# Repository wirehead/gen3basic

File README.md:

# gen3basic Wiring/Arduino compatible LED light board

This is a programmable light-painting instrument that looks enough like an Arduino board to use the Arduino studio and the Wiring library.  It has 3 through-hole 5mm LEDs, 3 5050 APA102 LEDs, 3 buttons, a set of screw terminals deliberately designed to be exactly like the terminals on a [PixelBlaze](https://www.bhencke.com/pixelblaze) for controlling external LED strings, and a non-shield-compatible set of breakout pins that are all on a 0.1" / 2.54mm grid.

## Prior art

I've got a pair of really old boards.  They both have 40 pin ATMega16's and some LEDs.  One has 8 LEDs so it works as a POV.  The other has 3 RGB LEDs.  I didn't really use them very much.

The things I did really wrong with them are:

 * No buttons!  This is actually really annoying because most of the standard modern buttons don't quite fit in a perfboard and so just finding buttons was annoying.  Therefore, I'd guess at what color I wanted as a pattern and then it wouldn't be right when I pulled it out during a shoot.
 * One of them was programmed in AVR assembler, the other one was programmed in AVR GCC.  No libraries.  The whole toolchain was a bit annoying and the problem is that I can do everything from scratch in assembly language and it's fun to play around with assembly language, but if you want to get something done, use the highest level tool that fits your needs.

## But first, why Prolific is a bunch of jerks

Anyway, the two boards moldered in my collection for a long time, then I decided that it was time to do some electronics stuff and pulled the cart that's always had my electronics on it out of the closet and set it up next to my computer, and started working on it again.

Really the only hitch is that apparently my Monoprice USB to Serial converter contains what may be a fake Prolific chip and Prolific's drivers were changed so as to intentionally not work with any of the fake chips by giving you an unhelpful error message.  So I had to get a new USB to serial cable.

Like, cool, I get that Prolific spent a lot of time and energy making a USB chip and they don't see any of the money from when some random factory decides to clone their chip.  But what this means for me is that Prolific took their annoyance upon parties who are not me out on me.

Also, FTDI has done the same thing.

So I was all set to do some AVR programming work, having rolled out my workbench cart with the STK-500 and my serial adapter... and then I had to hurry up and pick up another USB-to-RS232 cable.

## The design

Design goals:

 * Be useful for light painting
 * Have some single-spectrum LEDs in a commonly available size available.
 * Have some RGB LEDs also available.
 * Be able to control an external string of RGB LEDs.
 * Have some buttons for control, so I could switch programs.
 * Use some surface mount parts, but not do everything surface mount, so I wouldn't realize partway through fabbing the board that I'd made a poor life choice.
 * Be a 2 layer 5cm x 5cm board so I can fab it at places like DirtyPCB's.
 * Not be overly ambitious or complicated in any particular direction.
 * Be able to be programmed using a friendly Arduino environment.
 * Be able to be re-purposed as a general-purpose Arduino-esque design.
 * Not require me to have the full electronics workbench out to mess with it.

Various design thoughts:

 * Buttons!  Okay, so I've got the [PixelBlaze](https://www.bhencke.com/pixelblaze).  I've got a fully soldered and functional [MiniPOV 4 Kit](https://www.adafruit.com/product/1776) from Adafruit.  The MiniPOV is running up against a limit of how much EEPROM the AVR has so it really only can do one pattern.  The PixelBlaze is better because it's running equations and it's got WiFi anyway so I can just use a computer to tweak at the settings.  I decided to squeeze in 3 buttons because I know I need to change programs and I need to 'mute' the light so my lines can have a defined beginning and end and I'll probably really want to add at least one more later on.
 * Tactile cues are very important in the dark, which is why the corners all are different shapes and there's a pair of indents on the sides.  
 * I HATE LED MANUFACTURERS AND THEIR RANDOM SELECTION OF FOOTPRINTS.  Like, what I want is to pick a shape that lets me get at some LEDs that are available in a wide variety of colors other than the standard RGB wavelengths.  So I ended up just putting in the holes for 5mm because that still has a reasonably wide selection and no LED manufacturers screwing with the footprints.
 * There's a bunch of surface mount parts here.  I decided that, if you have a professionally manufactured PCB with solder masks and stuff, it's kinda silly to not use some 1206 or 0805 surface mount bits.
 * The reset circuitry fairly closely follows the Arduino model as well as the recommendations from AN2519, which suggests that you not only have a pull-up resistor but also a diode.
 * There are resistors in the MOSI and SCK nets, also a recommendation from AN2519, because otherwise it totally failed to work when I had it wired up on a breadboard with the AVR, the STK-500, and the APA102s.
 * Instead of a resonator like the Arduino, I use a crystal.  Mostly because it's kinda obvious that maybe I'd want to use it for a clock-like thing and a crystal is better for that.
 * I'm not putting an LED on the SCK line, which is one deviation from the standard Arduino form factor.  The last thing I want is a little glowing light while the APA's are being controlled and there's reasons why that's OK on a real Arduino and not mine.
 * I really want to make my board able to have a piece of perfboard with headers plugged in above it, which is one of several reasons why this is not using Arduino shields.  At the same time, the more pins I broke out, the harder the routing got, so I didn't break all of them out.
 * I meant to put a SOD-123 but I accidentally put a tiny SOD-323 instead.
 * Overall, I learned a lot from [Bald Engineer's DIY Arduino article](https://www.baldengineer.com/diy-arduino-schematic-checklist.html) and [Rheingold Heavy's Arduino From Scratch series](https://rheingoldheavy.com/category/education/fundamentals/arduino-from-scratch-series/).

I used [KiCad](http://kicad-pcb.org/) for schematic capture and PCB layout.

## BOM

| Reference    |  Quantity |  Value                                  |  Footprint                                                   |  Digi-Key_PN        |  Manufacturer_PN     |  Notes                                                                        |  Spec   | 
|--------------|-----------|-----------------------------------------|--------------------------------------------------------------|---------------------|----------------------|-------------------------------------------------------------------------------|---------| 
| C1 C2        | 2         | 22pF                                    | `Capacitor_SMD:C_0805_2012Metric_Pad1.15x1.40mm_HandSolder`    | 399-8036-1-ND       | C0805C220K5GACTU     |                                                                               | C0G     | 
| C3 C5 C7 C6  | 4         | 100nF                                   | `Capacitor_SMD:C_0805_2012Metric_Pad1.15x1.40mm_HandSolder`    | 1276-6840-1-ND      | CL21B104KCFNNNE      |                                                                               | X7R     | 
| C4 C8        | 2         | 47uF                                    | `Capacitor_THT:CP_Radial_D4.0mm_P1.50mm`                       | 493-12770-1-ND      | UVR1C470MDD6TP       |                                                                               | 20% 16V | 
| D1 D5 D4     | 3         | LED                                     | `LED_THT:LED_D5.0mm_Clear`                                     |                     |                      | Any random 5mm LED works, adjust matching resistor based on dropout voltage |         | 
| D2           | 1         | LED                                     | `LED_SMD:LED_0805_2012Metric_Pad1.15x1.40mm_HandSolder`        |                     |                      Any 0805 LED works, don't need to populate it                            |         | 
| D3           | 1         | 1N4148WS                                | `Diode_SMD:D_SOD-323`                                          |  1N4148WTPMSCT-ND   | 1N4148W-TP           |                                                                               |         | 
| D6 D7 D8     | 3         | APA102C                                 | `SparkFun-LED:APA102C                                        ` | 1568-1902-ND        | COM-14863            |                                                                               | 5050    | 
| H1 H2 H3     | 3         | MountingHole                            | `MountingHole:MountingHole_2.2mm_M2_ISO7380`                   |                     |                      |                                                                               |         | 
| J1           | 1         | Screw Terminal 01x02                    | `TerminalBlock:TerminalBlock_bornier-2_P5.08mm`                | ED2580-ND           | OSTTA024163          | Power                                                                         |         | 
| J2           | 1         | AVR-ISP-6                               | `Connector_PinHeader_2.54mm:PinHeader_2x03_P2.54mm_Vertical`   | 2057-PH2-06-UA-ND   | PH2-06-UA            | AVR-ISP                                                                       |         | 
| J3           | 1         | Conn 01x06                              | `Connector_PinHeader_2.54mm:PinHeader_1x06_P2.54mm_Vertical`   | 2057-PH1RA-06-UA-ND | PH1RA-06-UA          | Pins breakout                                                                 |         | 
| J4           | 1         | Conn 01x07                              | `Connector_PinHeader_2.54mm:PinHeader_1x07_P2.54mm_Vertical`   | S1012EC-07-ND       | PREC007SAAN-RC       | Pins breakout                                                                 |         | 
| J5           | 1         | Conn 01x08                              | `Connector_PinHeader_2.54mm:PinHeader_1x08_P2.54mm_Vertical`   | 2057-PH1RA-08-UA-ND | PH1RA-08-UA          | Pins breakout                                                                 |         | 
| J6           | 1         | Conn 01x06                              | `Connector_PinHeader_2.54mm:PinHeader_1x06_P2.54mm_Horizontal` | 2057-PH1RA-06-UA-ND |  PH1RA-06-UA         | FTDI-type serial connection                                                   |         | 
| J7           | 1         | Screw Terminal 01x04                    | `TerminalBlock:TerminalBlock_bornier-4_P5.08mm`                | ED2580-ND           | OSTTA024163          | Connecting to APA102 light strips.  Actually two pieces interlocked           |         | 
| R1           | 1         | 1M                                      | `Resistor_SMD:R_0805_2012Metric_Pad1.15x1.40mm_HandSolder`     | 541-1.0MAZCT-ND     | CRCW08051M00DHEAP    |                                                                               | 5%      | 
| R3 R2        | 2         | 330                                     | `Resistor_SMD:R_0805_2012Metric_Pad1.15x1.40mm_HandSolder`     | A106061CT-ND        | CRG0805F330R         |                                                                               | 5%      | 
| R4           | 1         | 1k                                      | `Resistor_SMD:R_0805_2012Metric_Pad1.15x1.40mm_HandSolder`     | RR12P1.0KDCT-ND     |  RR1220P-102-D       |                                                                               | 5%      | 
| R6           | 1         | 10k                                     | `Resistor_SMD:R_0805_2012Metric_Pad1.15x1.40mm_HandSolder`     | RR12P10.0KDCT-ND    | RR1220P-103-D        |                                                                               | 5%      | 
| R8 R5 R7     | 3         | 1k                                      | `Resistor_SMD:R_1206_3216Metric_Pad1.42x1.75mm_HandSolder`     | P1.0KECT-ND         | ERJ-8GEYJ102V        | Adjust to match LED                                                           | 5% 1/4W | 
| S1           | 1         | EG1224                                  | `Button_Switch_THT:SW_E-Switch_EG1224_SPDT_Angled`             | EG2585-ND           | EG1224               |                                                                               |         | 
| S3 S4 S2     | 3         | MOMENTARY-SWITCH-SPST-SMD-5.2-REDUNDANT | `SparkFun-Switches:TACTILE_SWITCH_SMD_5.2MM`                   | CKN10361CT-ND       | RS-187R05A2-DS MT RT |                                                                               |         | 
| U1           | 1         | ATMEGA328-PU                            | `Package_DIP:DIP-28_W7.62mm_Socket`                            | ATMEGA328-PU-ND     | ATMEGA328P-PU        | Can substitute ATMega8, 88, or 168.                                         |         | 
| Y1           | 1         | 16.0000MHZ 20PF                         | `Crystal:Crystal_HC49-U_Vertical`                              | 887-2015-ND         | 9B-16.000MBBK-B      | Can substitute other 20 pF crystal to change clock speed                      | 20 pF   | 

## Construction

I'm not going to write a tutorial, but here's some pointers:

 * This device is designed for the [MiniCore](https://github.com/MCUdude/MiniCore) so either before you insert the ATMega328 or using J2, you probably want to get that loaded.
 * I designed this to hand-solder the SMT parts.
 * You probably want a 28 pin socket to mount U1.
 * You may not want to populate all of the footprints, see usage below.  You almost certainly want to populate J1, J2, U1, Y1, C1, C2, C3, C4, C5, S1, R6, and D3 to get to a point where you can bootloader the CPU.  

## Usage

### Jacks

This device is designed for around 5v to J1.  There are no regulators or diodes so be careful.  My strategy at present is to connect with a USB cable to a USB power bank for power.

J2 is a 6-pin AVR-ISP programming connector.  While I'm assuming you'd want to use the MiniCore bootloader, you can use this port to make it a bootloader-less AVR or to program the bootloader for the first time.

J3, J4, and J5 are the useful pins of the AVR broken out.

J6 is the programming port, a FTDI-style 6 pin interface to plug a USB-to-serial converter in to.  It has auto-reset like a proper Arduino.

J7 mirrors the pinout of a [PixelBlaze](https://www.bhencke.com/pixelblaze).  You can power the device backwards via J7, which is probably most useful if you are driving a long LED string where this board's power usage is pretty much a footnote.

### Footprints you may want to leave unpopulated

Because you tend to get several PCBs and not just one, this is designed to have multiple useful configurations.  It is unlikely that you would ever want to populate all of the footprints.

 * You either want to populate J7 and control external APA102 strings or you want to populate D6-D8, as they are both reading from the same port.
 * D1, D4, and D5 are 5mm LEDs.  You want to use a resistor calculator to select a more appropriate value for R5, R7, and R8.  1k resistors should, at the very least, not melt any reasonably-valued LED.
 * If you are using this for light painting, you don't want to populate D2 (the little 0805 LED) or R4 (the resistor for D2).
 * Leaving the switches or LEDs unpopulated should be harmless.
 * C7 and C8 are decoupling for D6, D7, and D8.  You can probably leave them out if you aren't driving APA102's.

## License

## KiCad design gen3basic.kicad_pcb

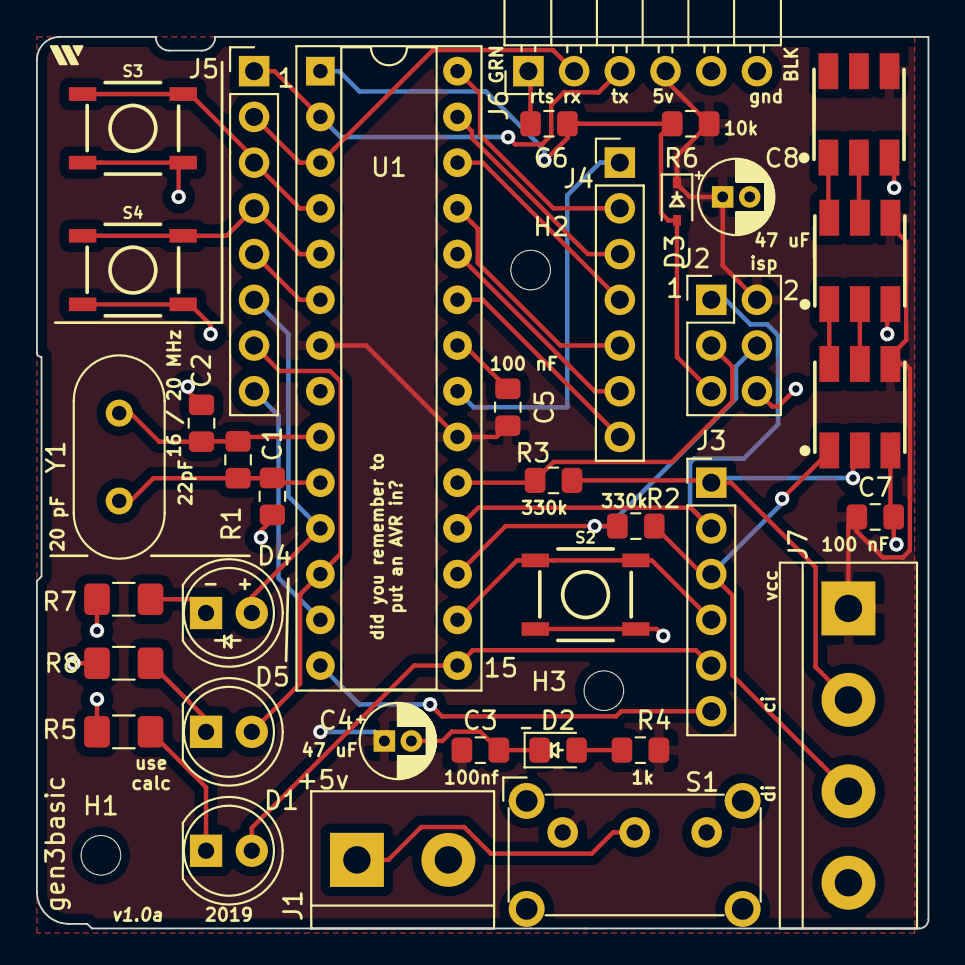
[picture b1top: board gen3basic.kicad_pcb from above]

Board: 2 copper layers, 49.5 x 49.5 mm, 40 parts (0 on the bottom side), 38 nets.

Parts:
C1, C2: 22pF; C_0805_2012Metric_Pad1.15x1.40mm_HandSolder
C3: 100nF; C_0805_2012Metric_Pad1.15x1.40mm_HandSolder
C4, C8: 47uF; CP_Radial_D4.0mm_P1.50mm
C5, C6, C7: 100 nF; C_0805_2012Metric_Pad1.15x1.40mm_HandSolder
D1, D4, D5: LED; LED_D5.0mm_Clear
D2: LED; LED_0805_2012Metric_Pad1.15x1.40mm_HandSolder
D3: 1N4148WS; D_SOD-323
D6, D7, D8: APA102C
H1, H2, H3: MountingHole; MountingHole_2.2mm_M2_ISO7380
J1: Screw_Terminal_01x02; TerminalBlock_bornier-2_P5.08mm
J2: AVR-ISP-6; PinHeader_2x03_P2.54mm_Vertical
J3: Conn_01x06; PinHeader_1x06_P2.54mm_Vertical
J4: Conn_01x07; PinHeader_1x07_P2.54mm_Vertical
J5: Conn_01x08; PinHeader_1x08_P2.54mm_Vertical
J6: Conn_01x06; PinHeader_1x06_P2.54mm_Horizontal
J7: Screw_Terminal_01x04; TerminalBlock_bornier-4_P5.08mm
R1: 1M; R_0805_2012Metric_Pad1.15x1.40mm_HandSolder
R2, R3: 330k; R_0805_2012Metric_Pad1.15x1.40mm_HandSolder
R4: 1k; R_0805_2012Metric_Pad1.15x1.40mm_HandSolder
R5, R7, R8: 1k; R_1206_3216Metric_Pad1.42x1.75mm_HandSolder
R6: 10k; R_0805_2012Metric_Pad1.15x1.40mm_HandSolder
S1: EG1224; SW_E-Switch_EG1224_SPDT_Angled
S2, S3, S4: MOMENTARY-SWITCH-SPST-SMD-5.2-REDUNDANT; TACTILE_SWITCH_SMD_5.2MM
U1: ATMEGA328-PU; DIP-28_W7.62mm_Socket
Y1: 16.0000MHZ 20PF; Crystal_HC49-U_Vertical

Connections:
/APA-CI: D6.2, J3.1, J7.2, R3.2
/APA-DI: D6.1, J3.3, J7.3, R2.2
/AREF: J4.1, U1.21
/DTR: C6.1, J6.1
/IN+: J1.1, S1.2
/LED1: D1.2, J3.5, U1.15
/LED2: D4.2, J5.6, U1.11
/LED3: D5.2, J5.7, U1.12
/MISO: J2.1, J3.2, U1.18
/MOSI: J2.4, R2.1, U1.17
/PB0: J3.6, U1.14
/PB2: J3.4, S2.1, S2.2, U1.16
/PB5: J2.3, R3.1, U1.19
/PC0: J4.7, U1.23
/PC1: J4.6, U1.24
/PC2: J4.5, U1.25
/PC3: J4.4, U1.26
/PC4: J4.3, U1.27
/PC5: J4.2, U1.28
/PD0-RXD: J5.1, J6.3, U1.2
/PD1-TXD: J5.2, J6.2, U1.3
/PD2: J5.3, S3.1, S3.2, U1.4
/PD3: J5.4, S4.1, S4.2, U1.5
/PD4: J5.5, U1.6
/PD7: J5.8, U1.13
/PWRLED: D2.2, R4.1
/RESET#: C6.2, D3.2, J2.5, R6.1, U1.1
GND: C1.1, C2.1, C3.2, C4.2, C5.2, C7.2, C8.2, D2.1, D6.3, D7.3, D8.3, J1.2, J2.6, J6.5, J6.6, J7.4, R5.2, R7.2, R8.2, S2.3, S2.4, S3.3, S3.4, S4.3, S4.4, U1.8, U1.22
unnamed: D1.1, R5.1
unnamed: D4.1, R7.1
unnamed: D5.1, R8.1
unnamed: D6.5, D7.2
unnamed: D6.6, D7.1
unnamed: D7.5, D8.2
unnamed: D7.6, D8.1
OSC1: C1.2, R1.2, U1.10, Y1.1
OSC2: C2.2, R1.1, U1.9, Y1.2
VCC: C3.1, C4.1, C5.1, C7.1, C8.1, D3.1, D6.4, D7.4, D8.4, J2.2, J6.4, J7.1, R4.2, R6.2, S1.1, U1.7, U1.20

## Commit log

2019-05-19 initial commit.
2019-06-01 moved a bunch of stuff around.
2019-06-09 fixing footprints, final design verification, silkscreen.
2020-05-02 update.
2020-05-02 add pdf.

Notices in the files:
README.md:
License:
[License: CC BY-SA 4.0](https://creativecommons.org/licenses/by-sa/4.0/)
